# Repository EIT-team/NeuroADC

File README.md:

# NeuroADC
Open Source data acquisition system for biopotential recording and Fast Neural EIT, originally developed by Dr. Enrico Ravagli in 2026.
Contributions are welcome under GPL-3.0 license.

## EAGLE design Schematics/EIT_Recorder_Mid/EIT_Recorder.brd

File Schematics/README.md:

# Schematics
- This subfolder contains design files for the three Printed Circuit Boards which make up the NeuroADC device. Board names are based on their physical location when assembled (top/mid/bottom)
- Boards have been designed using Cad software EAGLE. With EAGLE now being decommissioned in June 2026, board files can be opened and edited in Autodesk Fusion.

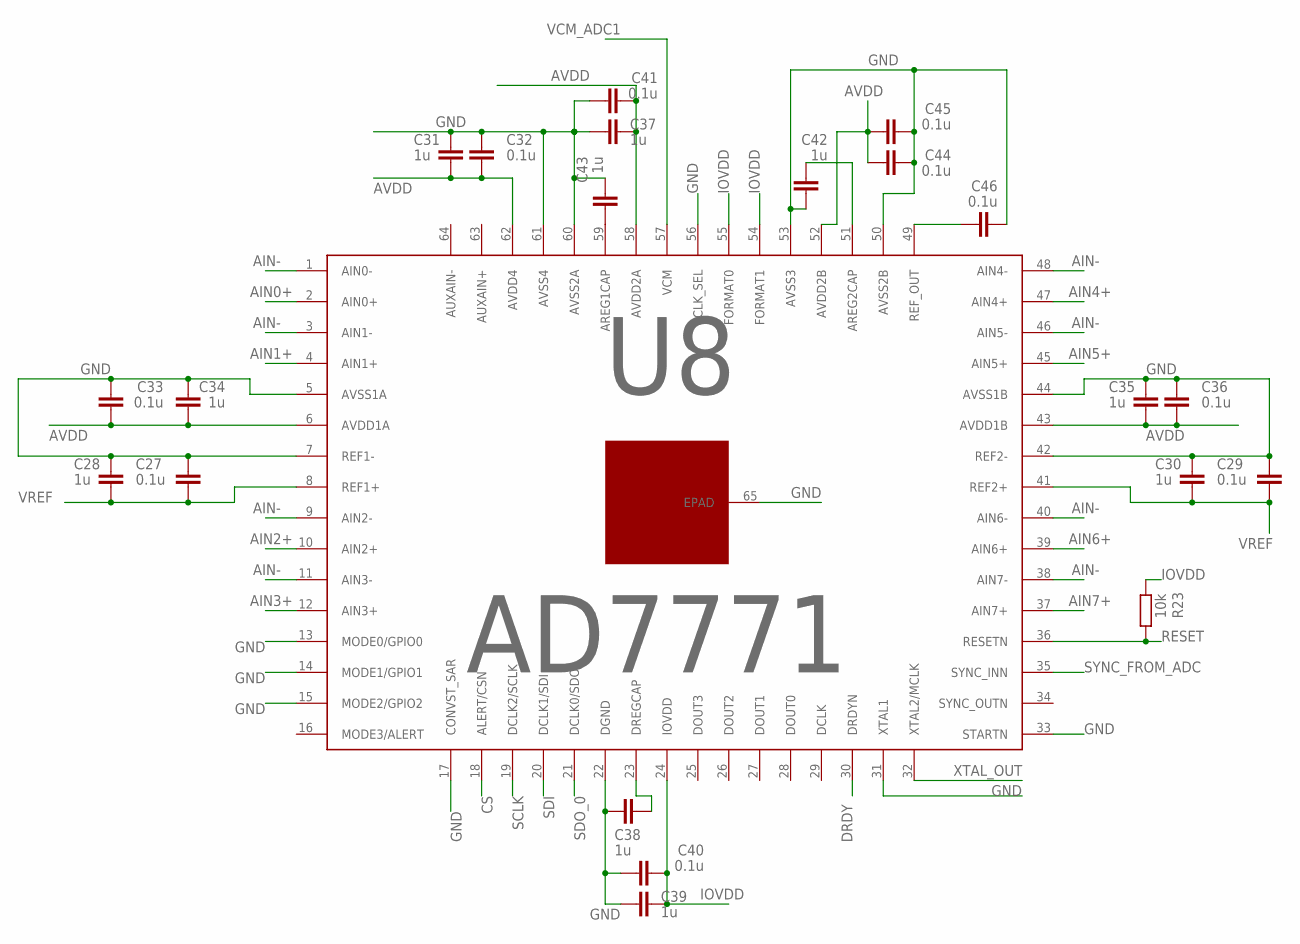
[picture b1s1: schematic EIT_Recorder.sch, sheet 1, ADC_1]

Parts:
C27, C29, C32, C33, C36, C40, C41, C44, C45, C46: 0.1u; C0402
C28, C30, C31, C34, C35, C37, C38, C39, C42, C43: 1u; C0402
R23: 10k; R0603
U8: AD7771; LFCSP64_CUSTOM

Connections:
AIN0+: U8.2 (AIN0+); also elsewhere on the board
AIN1+: U8.4 (AIN1+); also elsewhere on the board
AIN2+: U8.10 (AIN2+); also elsewhere on the board
AIN3+: U8.12 (AIN3+); also elsewhere on the board
AIN4+: U8.47 (AIN4+); also elsewhere on the board
AIN5+: U8.45 (AIN5+); also elsewhere on the board
AIN6+: U8.39 (AIN6+); also elsewhere on the board
AIN7+: U8.37 (AIN7+); also elsewhere on the board
AIN-: U8.1 (AIN0-), U8.3 (AIN1-), U8.9 (AIN2-), U8.11 (AIN3-), U8.38 (AIN7-), U8.40 (AIN6-), U8.46 (AIN5-), U8.48 (AIN4-); also elsewhere on the board
AVDD: C31.1, C32.1, C33.1, C34.1, C35.1, C36.1, C37.1, C41.1, C44.2, C45.2, U8.6 (AVDD1A), U8.43 (AVDD1B), U8.52 (AVDD2B), U8.58 (AVDD2A), U8.62 (AVDD4); also elsewhere on the board
CS: U8.18 (ALERT/CSN); also elsewhere on the board
DRDY: U8.30 (DRDYN); also elsewhere on the board
GND: C27.2, C28.2, C29.2, C30.2, C31.2, C32.2, C33.2, C34.2, C35.2, C36.2, C37.2, C38.1, C39.2, C40.2, C41.2, C42.2, C43.1, C44.1, C45.1, C46.1, U8.5 (AVSS1A), U8.7 (REF1-), U8.13 (MODE0/GPIO0), U8.14 (MODE1/GPIO1), U8.15 (MODE2/GPIO2), U8.17 (CONVST_SAR), U8.22 (DGND), U8.31 (XTAL1), U8.33 (STARTN), U8.42 (REF2-), U8.44 (AVSS1B), U8.50 (AVSS2B), U8.53 (AVSS3), U8.56 (CLK_SEL), U8.60 (AVSS2A), U8.61 (AVSS4), U8.65 (EPAD); also elsewhere on the board
IOVDD: C39.1, C40.1, R23.2, U8.24 (IOVDD), U8.54 (FORMAT1), U8.55 (FORMAT0); also elsewhere on the board
unnamed: C43.2, U8.59 (AREG1CAP)
unnamed: C38.2, U8.23 (DREGCAP)
unnamed: C46.2, U8.49 (REF_OUT)
unnamed: C42.1, U8.51 (AREG2CAP)
RESET: R23.1, U8.36 (RESETN); also elsewhere on the board
SCLK: U8.19 (DCLK2/SCLK); also elsewhere on the board
SDI: U8.20 (DCLK1/SDI); also elsewhere on the board
SDO_0: U8.21 (DCLK0/SDO); also elsewhere on the board
SYNC_FROM_ADC: U8.35 (SYNC_INN); also elsewhere on the board
VCM_ADC1: U8.57 (VCM); also elsewhere on the board
VREF: C27.1, C28.1, C29.1, C30.1, U8.8 (REF1+), U8.41 (REF2+); also elsewhere on the board
XTAL_OUT: U8.32 (XTAL2/MCLK); also elsewhere on the board

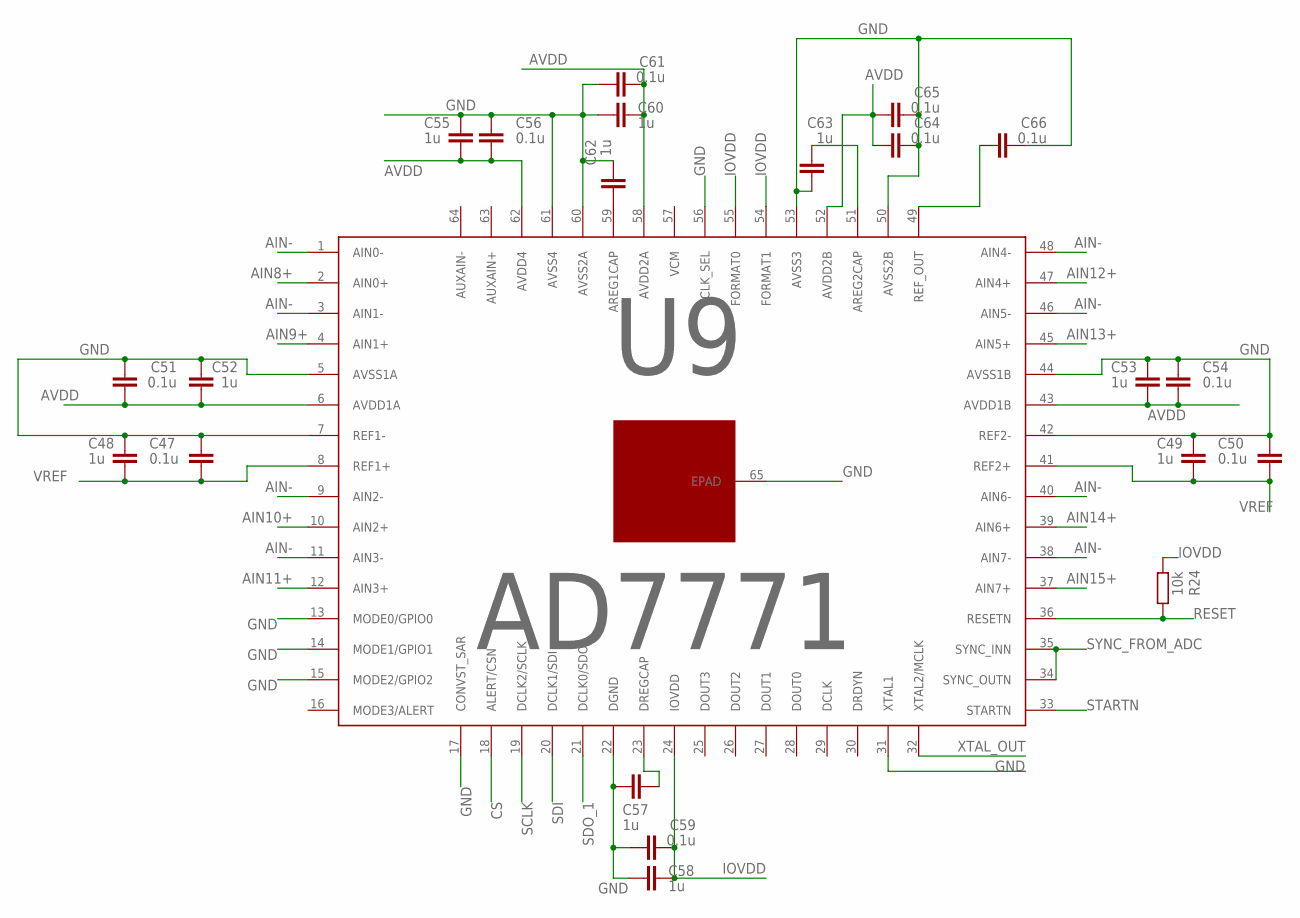
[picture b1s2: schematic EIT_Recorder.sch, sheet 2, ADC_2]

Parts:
C47, C50, C51, C54, C56, C59, C61, C64, C65, C66: 0.1u; C0402
C48, C49, C52, C53, C55, C57, C58, C60, C62, C63: 1u; C0402
R24: 10k; R0603
U9: AD7771; LFCSP64_CUSTOM

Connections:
AIN8+: U9.2 (AIN0+); also elsewhere on the board
AIN9+: U9.4 (AIN1+); also elsewhere on the board
AIN10+: U9.10 (AIN2+); also elsewhere on the board
AIN11+: U9.12 (AIN3+); also elsewhere on the board
AIN12+: U9.47 (AIN4+); also elsewhere on the board
AIN13+: U9.45 (AIN5+); also elsewhere on the board
AIN14+: U9.39 (AIN6+); also elsewhere on the board
AIN15+: U9.37 (AIN7+); also elsewhere on the board
AIN-: U9.1 (AIN0-), U9.3 (AIN1-), U9.9 (AIN2-), U9.11 (AIN3-), U9.38 (AIN7-), U9.40 (AIN6-), U9.46 (AIN5-), U9.48 (AIN4-); also elsewhere on the board
AVDD: C51.1, C52.1, C53.1, C54.1, C55.1, C56.1, C60.1, C61.1, C64.2, C65.2, U9.6 (AVDD1A), U9.43 (AVDD1B), U9.52 (AVDD2B), U9.58 (AVDD2A), U9.62 (AVDD4); also elsewhere on the board
CS: U9.18 (ALERT/CSN); also elsewhere on the board
GND: C47.2, C48.2, C49.2, C50.2, C51.2, C52.2, C53.2, C54.2, C55.2, C56.2, C57.1, C58.2, C59.2, C60.2, C61.2, C62.1, C63.2, C64.1, C65.1, C66.1, U9.5 (AVSS1A), U9.7 (REF1-), U9.13 (MODE0/GPIO0), U9.14 (MODE1/GPIO1), U9.15 (MODE2/GPIO2), U9.17 (CONVST_SAR), U9.22 (DGND), U9.31 (XTAL1), U9.42 (REF2-), U9.44 (AVSS1B), U9.50 (AVSS2B), U9.53 (AVSS3), U9.56 (CLK_SEL), U9.60 (AVSS2A), U9.61 (AVSS4), U9.65 (EPAD); also elsewhere on the board
IOVDD: C58.1, C59.1, R24.2, U9.24 (IOVDD), U9.54 (FORMAT1), U9.55 (FORMAT0); also elsewhere on the board
unnamed: C57.2, U9.23 (DREGCAP)
unnamed: C62.2, U9.59 (AREG1CAP)
unnamed: C63.1, U9.51 (AREG2CAP)
unnamed: C66.2, U9.49 (REF_OUT)
RESET: R24.1, U9.36 (RESETN); also elsewhere on the board
SCLK: U9.19 (DCLK2/SCLK); also elsewhere on the board
SDI: U9.20 (DCLK1/SDI); also elsewhere on the board
SDO_1: U9.21 (DCLK0/SDO); also elsewhere on the board
STARTN: U9.33 (STARTN); also elsewhere on the board
SYNC_FROM_ADC: U9.34 (SYNC_OUTN), U9.35 (SYNC_INN); also elsewhere on the board
VREF: C47.1, C48.1, C49.1, C50.1, U9.8 (REF1+), U9.41 (REF2+); also elsewhere on the board
XTAL_OUT: U9.32 (XTAL2/MCLK); also elsewhere on the board

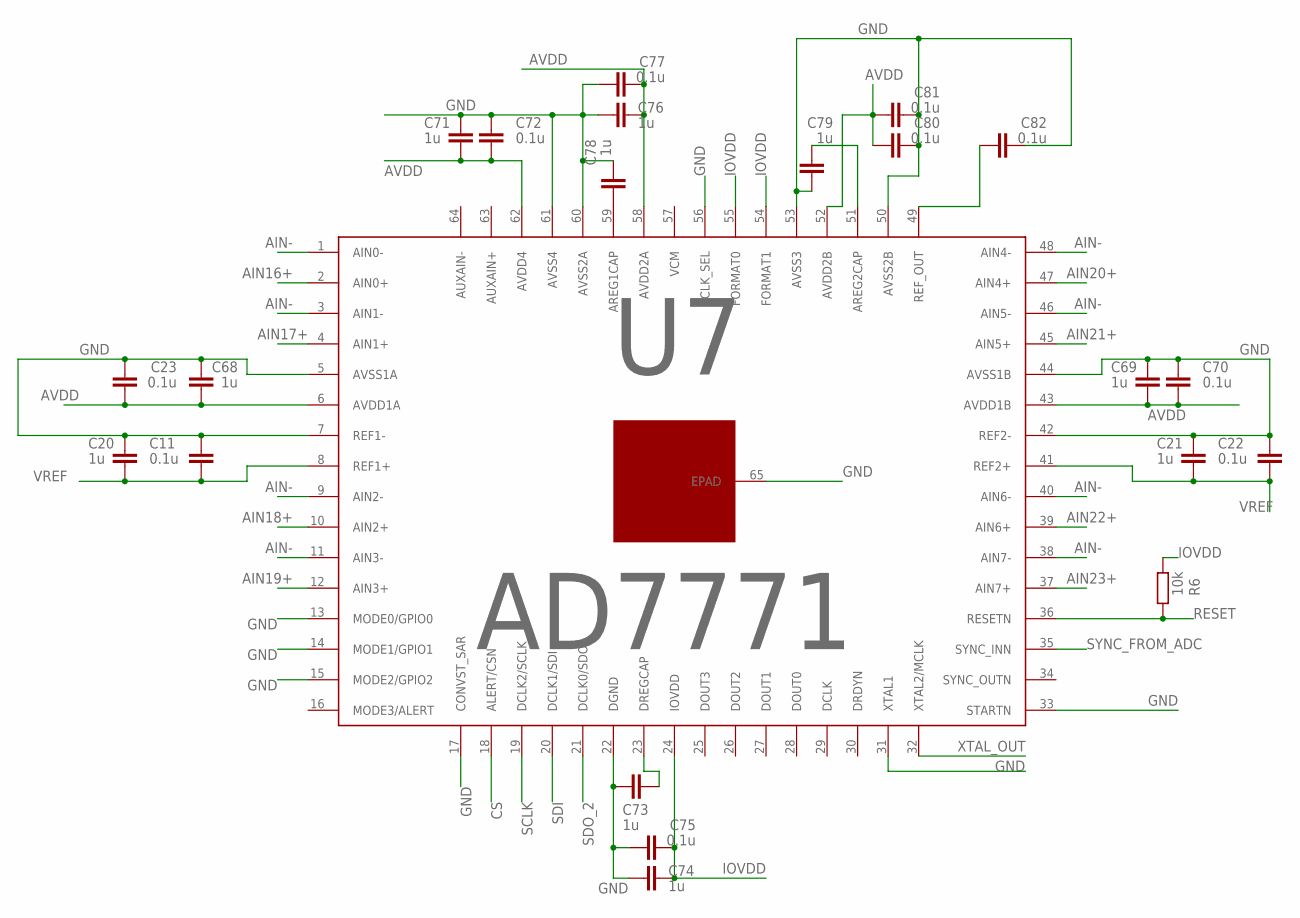
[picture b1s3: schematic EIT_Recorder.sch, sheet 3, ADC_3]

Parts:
C11, C22, C23, C70, C72, C75, C77, C80, C81, C82: 0.1u; C0402
C20, C21, C68, C69, C71, C73, C74, C76, C78, C79: 1u; C0402
R6: 10k; R0603
U7: AD7771; LFCSP64_CUSTOM

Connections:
AIN16+: U7.2 (AIN0+); also elsewhere on the board
AIN17+: U7.4 (AIN1+); also elsewhere on the board
AIN18+: U7.10 (AIN2+); also elsewhere on the board
AIN19+: U7.12 (AIN3+); also elsewhere on the board
AIN20+: U7.47 (AIN4+); also elsewhere on the board
AIN21+: U7.45 (AIN5+); also elsewhere on the board
AIN22+: U7.39 (AIN6+); also elsewhere on the board
AIN23+: U7.37 (AIN7+); also elsewhere on the board
AIN-: U7.1 (AIN0-), U7.3 (AIN1-), U7.9 (AIN2-), U7.11 (AIN3-), U7.38 (AIN7-), U7.40 (AIN6-), U7.46 (AIN5-), U7.48 (AIN4-); also elsewhere on the board
AVDD: C23.1, C68.1, C69.1, C70.1, C71.1, C72.1, C76.1, C77.1, C80.2, C81.2, U7.6 (AVDD1A), U7.43 (AVDD1B), U7.52 (AVDD2B), U7.58 (AVDD2A), U7.62 (AVDD4); also elsewhere on the board
CS: U7.18 (ALERT/CSN); also elsewhere on the board
GND: C11.2, C20.2, C21.2, C22.2, C23.2, C68.2, C69.2, C70.2, C71.2, C72.2, C73.1, C74.2, C75.2, C76.2, C77.2, C78.1, C79.2, C80.1, C81.1, C82.1, U7.5 (AVSS1A), U7.7 (REF1-), U7.13 (MODE0/GPIO0), U7.14 (MODE1/GPIO1), U7.15 (MODE2/GPIO2), U7.17 (CONVST_SAR), U7.22 (DGND), U7.31 (XTAL1), U7.33 (STARTN), U7.42 (REF2-), U7.44 (AVSS1B), U7.50 (AVSS2B), U7.53 (AVSS3), U7.56 (CLK_SEL), U7.60 (AVSS2A), U7.61 (AVSS4), U7.65 (EPAD); also elsewhere on the board
IOVDD: C74.1, C75.1, R6.2, U7.24 (IOVDD), U7.54 (FORMAT1), U7.55 (FORMAT0); also elsewhere on the board
unnamed: C73.2, U7.23 (DREGCAP)
unnamed: C78.2, U7.59 (AREG1CAP)
unnamed: C79.1, U7.51 (AREG2CAP)
unnamed: C82.2, U7.49 (REF_OUT)
RESET: R6.1, U7.36 (RESETN); also elsewhere on the board
SCLK: U7.19 (DCLK2/SCLK); also elsewhere on the board
SDI: U7.20 (DCLK1/SDI); also elsewhere on the board
SDO_2: U7.21 (DCLK0/SDO); also elsewhere on the board
SYNC_FROM_ADC: U7.35 (SYNC_INN); also elsewhere on the board
VREF: C11.1, C20.1, C21.1, C22.1, U7.8 (REF1+), U7.41 (REF2+); also elsewhere on the board
XTAL_OUT: U7.32 (XTAL2/MCLK); also elsewhere on the board

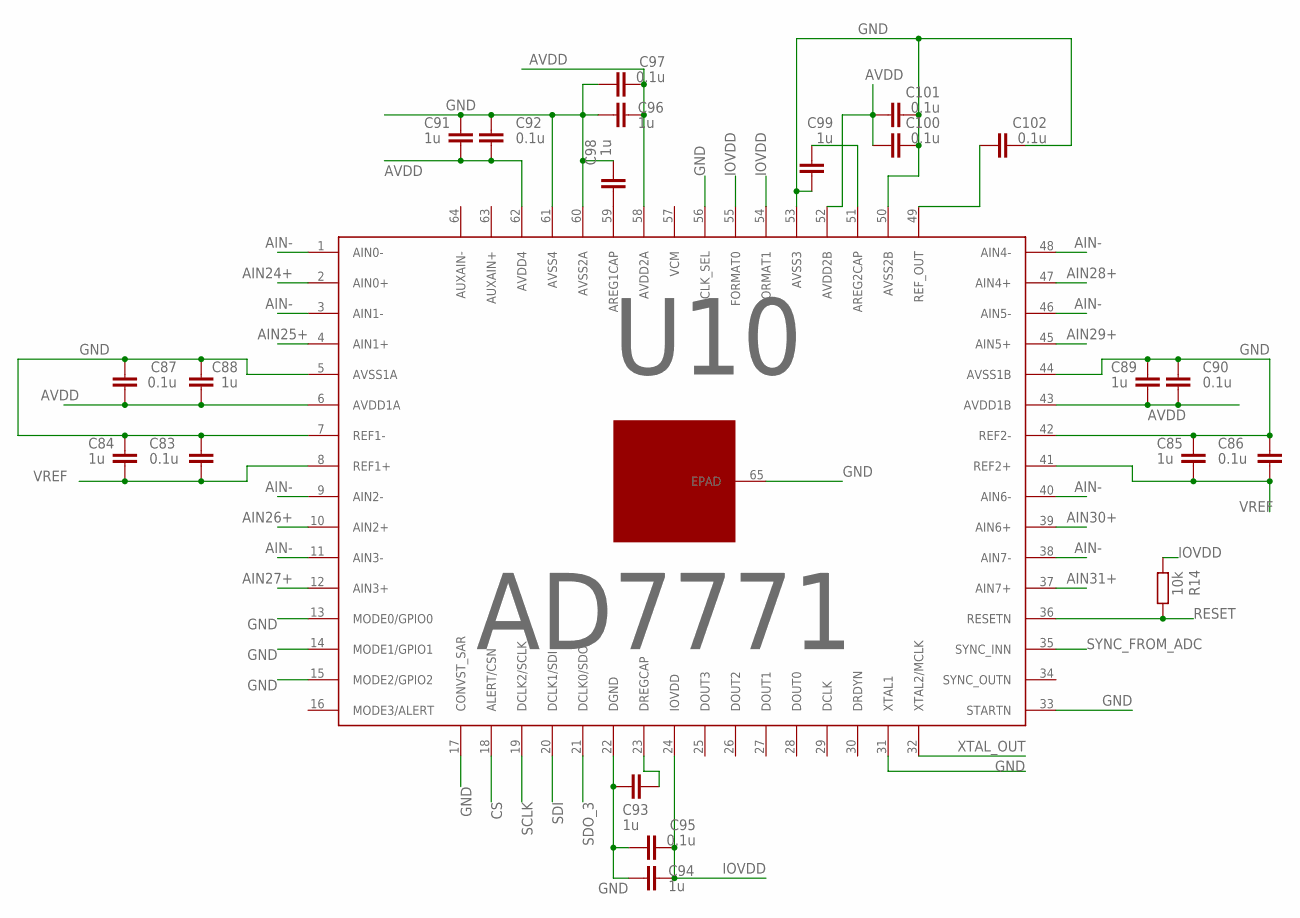
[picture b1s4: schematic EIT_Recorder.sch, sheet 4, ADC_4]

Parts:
C83, C86, C87, C90, C92, C95, C97, C100, C101, C102: 0.1u; C0402
C84, C85, C88, C89, C91, C93, C94, C96, C98, C99: 1u; C0402
R14: 10k; R0603
U10: AD7771; LFCSP64_CUSTOM

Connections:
AIN24+: U10.2 (AIN0+); also elsewhere on the board
AIN25+: U10.4 (AIN1+); also elsewhere on the board
AIN26+: U10.10 (AIN2+); also elsewhere on the board
AIN27+: U10.12 (AIN3+); also elsewhere on the board
AIN28+: U10.47 (AIN4+); also elsewhere on the board
AIN29+: U10.45 (AIN5+); also elsewhere on the board
AIN30+: U10.39 (AIN6+); also elsewhere on the board
AIN31+: U10.37 (AIN7+); also elsewhere on the board
AIN-: U10.1 (AIN0-), U10.3 (AIN1-), U10.9 (AIN2-), U10.11 (AIN3-), U10.38 (AIN7-), U10.40 (AIN6-), U10.46 (AIN5-), U10.48 (AIN4-); also elsewhere on the board
AVDD: C87.1, C88.1, C89.1, C90.1, C91.1, C92.1, C96.1, C97.1, C100.2, C101.2, U10.6 (AVDD1A), U10.43 (AVDD1B), U10.52 (AVDD2B), U10.58 (AVDD2A), U10.62 (AVDD4); also elsewhere on the board
CS: U10.18 (ALERT/CSN); also elsewhere on the board
GND: C83.2, C84.2, C85.2, C86.2, C87.2, C88.2, C89.2, C90.2, C91.2, C92.2, C93.1, C94.2, C95.2, C96.2, C97.2, C98.1, C99.2, C100.1, C101.1, C102.1, U10.5 (AVSS1A), U10.7 (REF1-), U10.13 (MODE0/GPIO0), U10.14 (MODE1/GPIO1), U10.15 (MODE2/GPIO2), U10.17 (CONVST_SAR), U10.22 (DGND), U10.31 (XTAL1), U10.33 (STARTN), U10.42 (REF2-), U10.44 (AVSS1B), U10.50 (AVSS2B), U10.53 (AVSS3), U10.56 (CLK_SEL), U10.60 (AVSS2A), U10.61 (AVSS4), U10.65 (EPAD); also elsewhere on the board
IOVDD: C94.1, C95.1, R14.2, U10.24 (IOVDD), U10.54 (FORMAT1), U10.55 (FORMAT0); also elsewhere on the board
unnamed: C93.2, U10.23 (DREGCAP)
unnamed: C98.2, U10.59 (AREG1CAP)
unnamed: C99.1, U10.51 (AREG2CAP)
unnamed: C102.2, U10.49 (REF_OUT)
RESET: R14.1, U10.36 (RESETN); also elsewhere on the board
SCLK: U10.19 (DCLK2/SCLK); also elsewhere on the board
SDI: U10.20 (DCLK1/SDI); also elsewhere on the board
SDO_3: U10.21 (DCLK0/SDO); also elsewhere on the board
SYNC_FROM_ADC: U10.35 (SYNC_INN); also elsewhere on the board
VREF: C83.1, C84.1, C85.1, C86.1, U10.8 (REF1+), U10.41 (REF2+); also elsewhere on the board
XTAL_OUT: U10.32 (XTAL2/MCLK); also elsewhere on the board

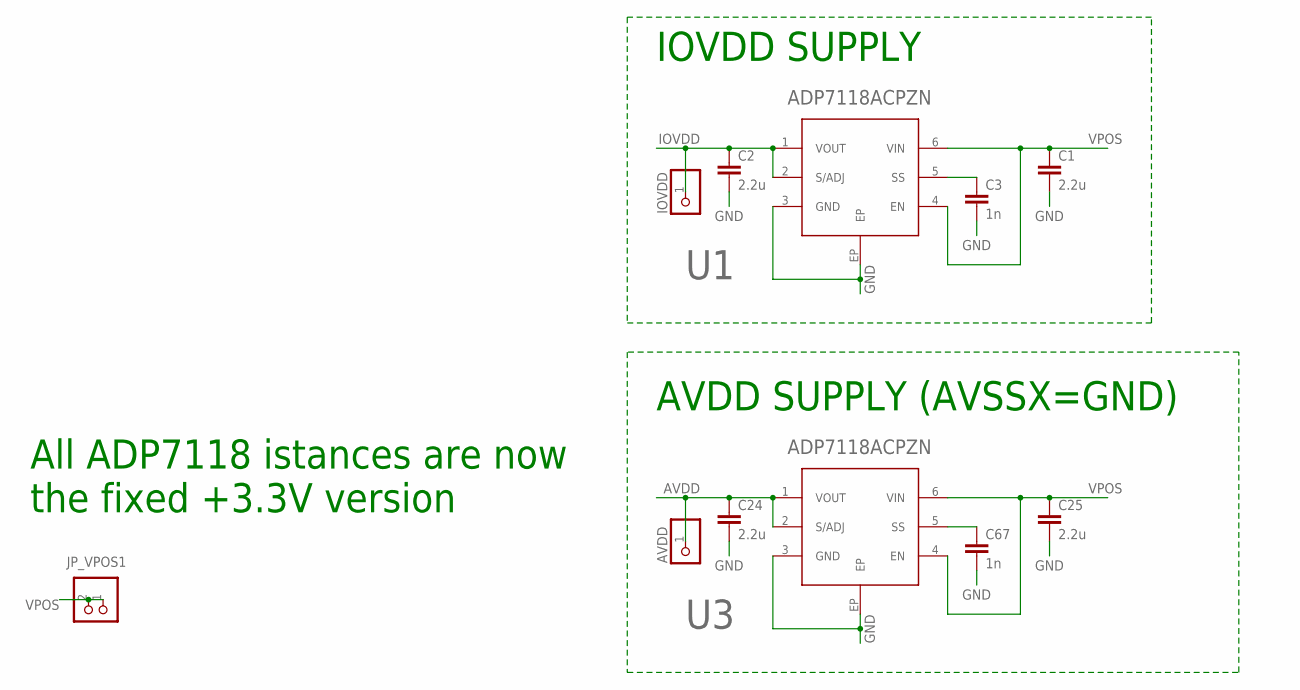
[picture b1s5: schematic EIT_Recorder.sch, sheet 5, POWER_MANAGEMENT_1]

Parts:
AVDD: PINHD-1X1; 1X01
C1, C2, C24, C25: 2.2u; C0603
C3, C67: 1n; C0402
IOVDD: PINHD-1X1; 1X01
JP_VPOS1: PINHD-1X2; 1X02
U1, U3: ADP7118ACPZN; LFCSP6_CUSTOM

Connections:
AVDD: AVDD.1, C24.1, U3.1 (VOUT), U3.2 (S/ADJ); also elsewhere on the board
GND: C1.2, C2.2, C3.2, C24.2, C25.2, C67.2, U1.3 (GND), U1.EP, U3.3 (GND), U3.EP; also elsewhere on the board
IOVDD: C2.1, IOVDD.1, U1.1 (VOUT), U1.2 (S/ADJ); also elsewhere on the board
unnamed: C3.1, U1.5 (SS)
unnamed: C67.1, U3.5 (SS)
VPOS: C1.1, C25.1, JP_VPOS1.1, JP_VPOS1.2, U1.4 (EN), U1.6 (VIN), U3.4 (EN), U3.6 (VIN); also elsewhere on the board

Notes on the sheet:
IOVDD SUPPLY
AVDD SUPPLY (AVSSX=GND)
All ADP7118 istances are now the fixed +3.3V version

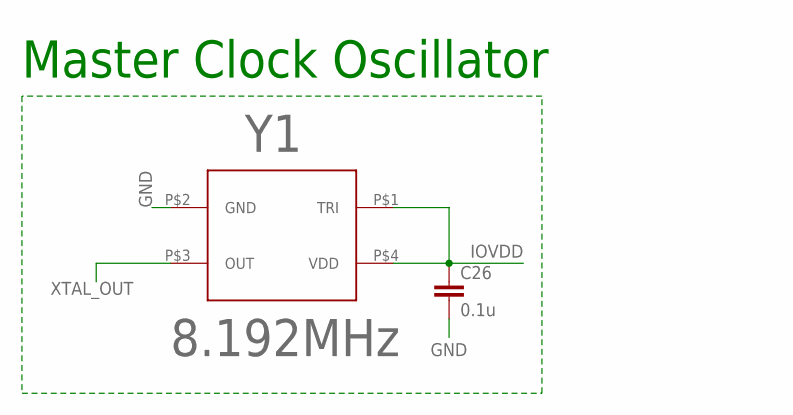
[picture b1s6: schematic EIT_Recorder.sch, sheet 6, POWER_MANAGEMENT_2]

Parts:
C26: 0.1u; C0402
Y1: 8.192MHz; ECS-2520MVLC

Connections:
GND: C26.2, Y1.P$2 (GND); also elsewhere on the board
IOVDD: C26.1, Y1.P$1 (TRI), Y1.P$4 (VDD); also elsewhere on the board
XTAL_OUT: Y1.P$3 (OUT); also elsewhere on the board

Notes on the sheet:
Master Clock Oscillator

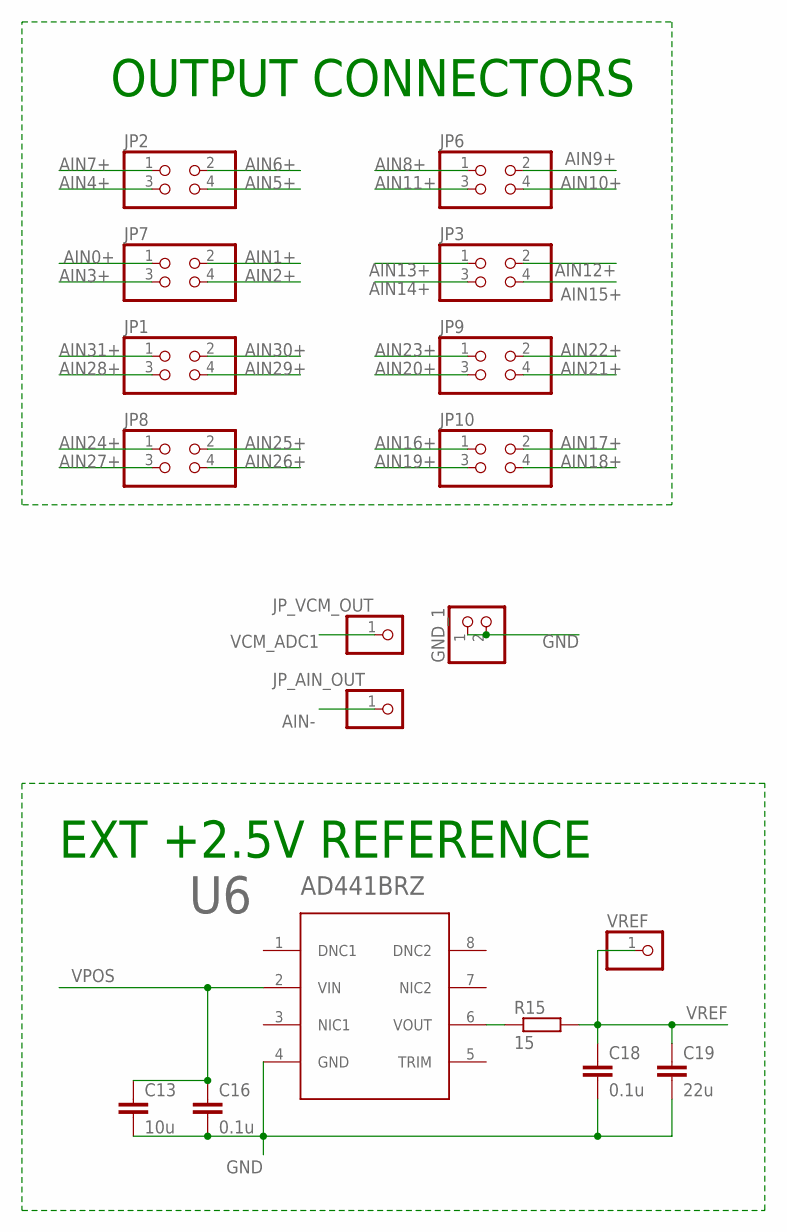
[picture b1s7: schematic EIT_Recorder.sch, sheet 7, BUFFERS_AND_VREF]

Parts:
C13: 10u; C0805
C16, C18: 0.1u; C0402
C19: 22u; C0805
GND_1: PINHD-1X2; 1X02
JP1, JP2, JP3, JP6, JP7, JP8, JP9, JP10: PINHD-2X2; 2X02
JP_AIN_OUT: PINHD-1X1; 1X01
JP_VCM_OUT: PINHD-1X1; 1X01
R15: 15; R0603
U6: AD441BRZ; SOIC8N_CUSTOM
VREF: PINHD-1X1; 1X01

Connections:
AIN0+: JP7.1; also elsewhere on the board
AIN1+: JP7.2; also elsewhere on the board
AIN2+: JP7.4; also elsewhere on the board
AIN3+: JP7.3; also elsewhere on the board
AIN4+: JP2.3; also elsewhere on the board
AIN5+: JP2.4; also elsewhere on the board
AIN6+: JP2.2; also elsewhere on the board
AIN7+: JP2.1; also elsewhere on the board
AIN8+: JP6.1; also elsewhere on the board
AIN9+: JP6.2; also elsewhere on the board
AIN10+: JP6.4; also elsewhere on the board
AIN11+: JP6.3; also elsewhere on the board
AIN12+: JP3.2; also elsewhere on the board
AIN13+: JP3.1; also elsewhere on the board
AIN14+: JP3.3; also elsewhere on the board
AIN15+: JP3.4; also elsewhere on the board
AIN16+: JP10.1; also elsewhere on the board
AIN17+: JP10.2; also elsewhere on the board
AIN18+: JP10.4; also elsewhere on the board
AIN19+: JP10.3; also elsewhere on the board
AIN20+: JP9.3; also elsewhere on the board
AIN21+: JP9.4; also elsewhere on the board
AIN22+: JP9.2; also elsewhere on the board
AIN23+: JP9.1; also elsewhere on the board
AIN24+: JP8.1; also elsewhere on the board
AIN25+: JP8.2; also elsewhere on the board
AIN26+: JP8.4; also elsewhere on the board
AIN27+: JP8.3; also elsewhere on the board
AIN28+: JP1.3; also elsewhere on the board
AIN29+: JP1.4; also elsewhere on the board
AIN30+: JP1.2; also elsewhere on the board
AIN31+: JP1.1; also elsewhere on the board
AIN-: JP_AIN_OUT.1; also elsewhere on the board
GND: C13.2, C16.2, C18.2, C19.2, GND_1.1, GND_1.2, U6.4 (GND); also elsewhere on the board
unnamed: R15.1, U6.6 (VOUT)
VCM_ADC1: JP_VCM_OUT.1; also elsewhere on the board
VPOS: C13.1, C16.1, U6.2 (VIN); also elsewhere on the board
VREF: C18.1, C19.1, R15.2, VREF.1; also elsewhere on the board

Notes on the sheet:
EXT +2.5V REFERENCE
OUTPUT CONNECTORS

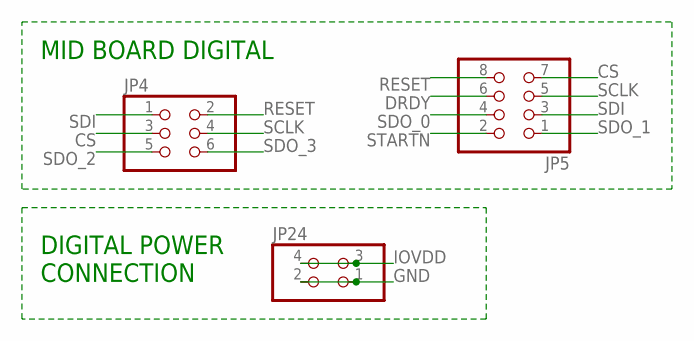
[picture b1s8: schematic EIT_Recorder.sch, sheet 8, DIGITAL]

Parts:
JP4: PINHD-2X3; 2X03
JP5: PINHD-2X4; 2X04
JP24: PINHD-2X2; 2X02

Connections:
CS: JP4.3, JP5.7; also elsewhere on the board
DRDY: JP5.6; also elsewhere on the board
GND: JP24.1, JP24.2; also elsewhere on the board
IOVDD: JP24.3, JP24.4; also elsewhere on the board
RESET: JP4.2, JP5.8; also elsewhere on the board
SCLK: JP4.4, JP5.5; also elsewhere on the board
SDI: JP4.1, JP5.3; also elsewhere on the board
SDO_0: JP5.4; also elsewhere on the board
SDO_1: JP5.1; also elsewhere on the board
SDO_2: JP4.5; also elsewhere on the board
SDO_3: JP4.6; also elsewhere on the board
STARTN: JP5.2; also elsewhere on the board

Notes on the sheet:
MID BOARD DIGITAL
DIGITAL POWER CONNECTION

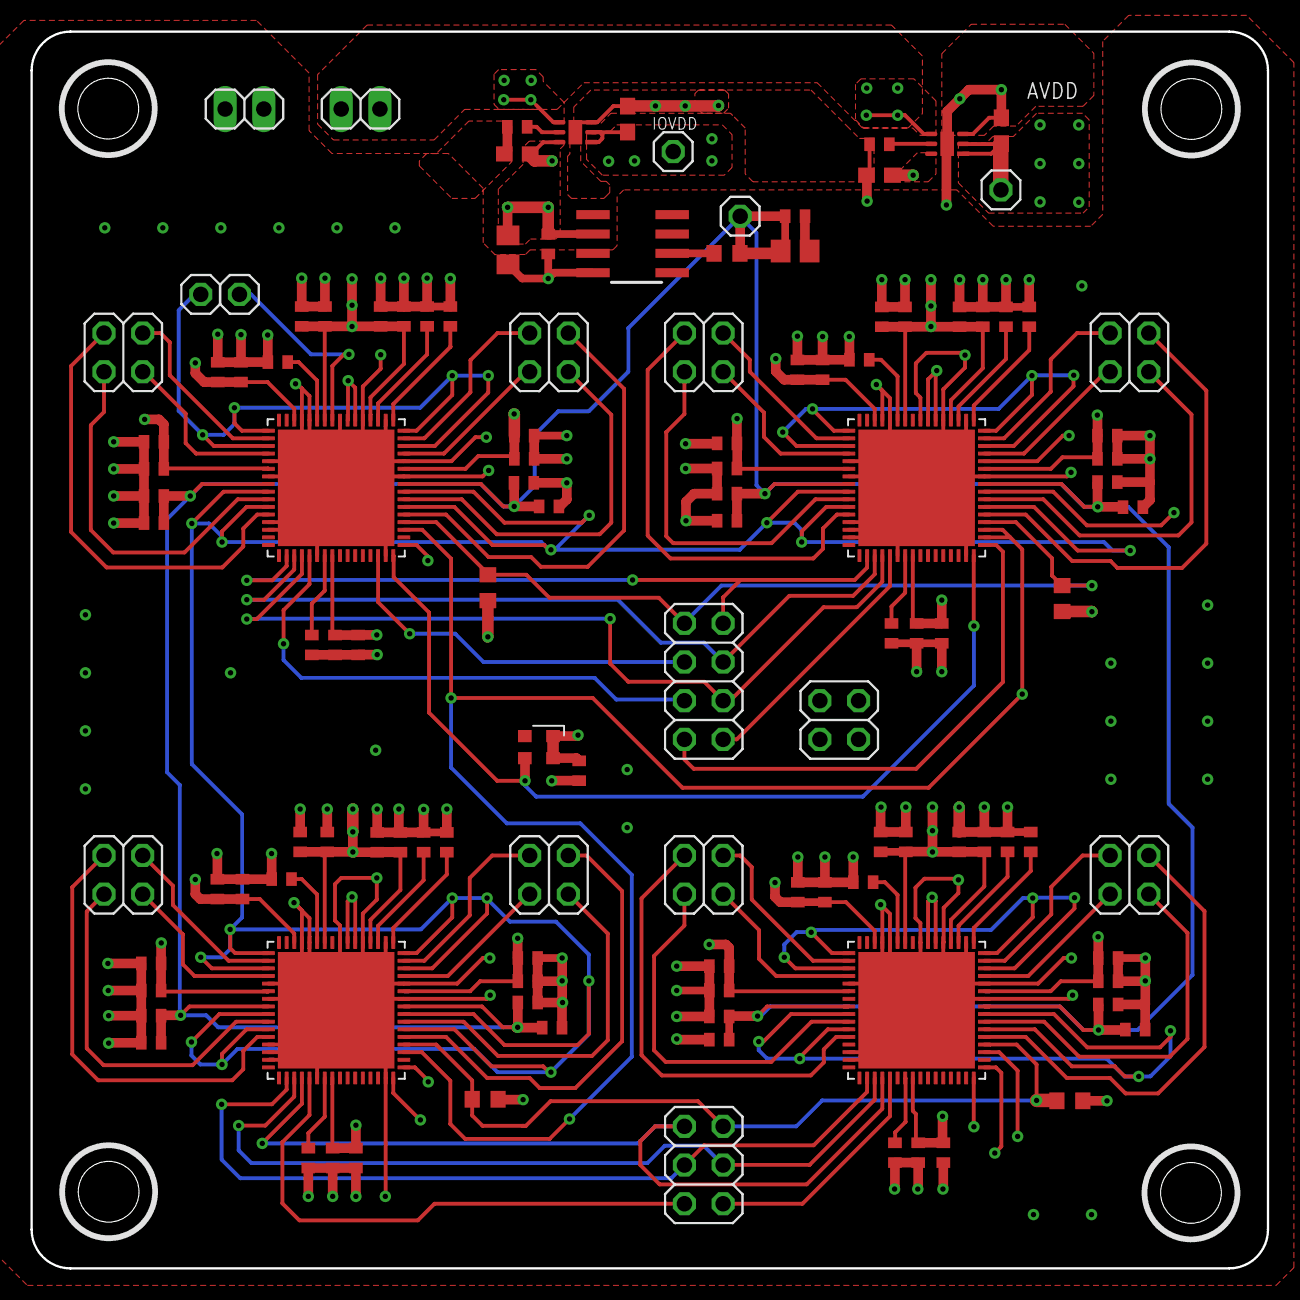
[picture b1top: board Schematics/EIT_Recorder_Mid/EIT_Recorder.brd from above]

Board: 6 copper layers, 81.2 x 81.2 mm, 122 parts (0 on the bottom side), 70 nets.

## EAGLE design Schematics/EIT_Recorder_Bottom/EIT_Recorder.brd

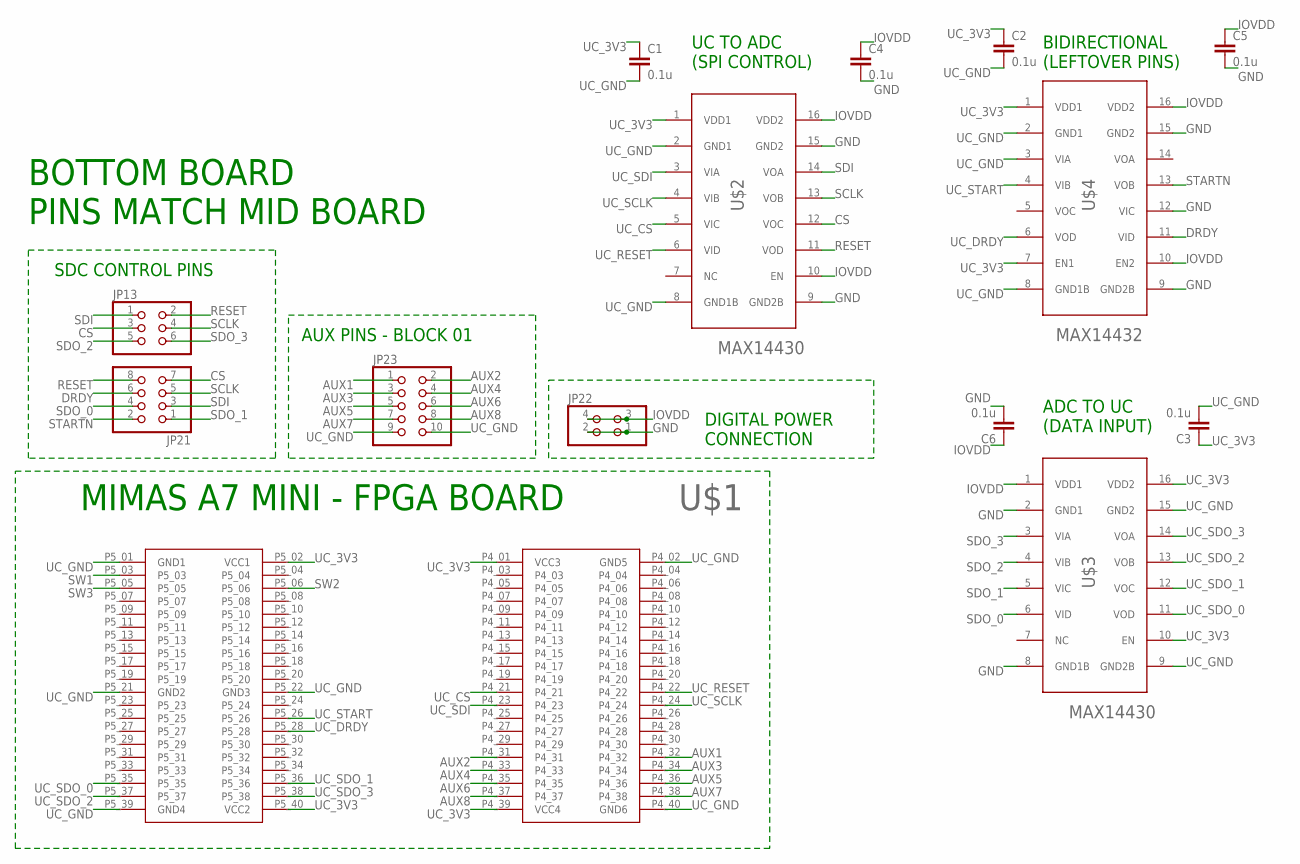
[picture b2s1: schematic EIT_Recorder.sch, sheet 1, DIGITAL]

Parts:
C1, C2, C3, C4, C5, C6: 0.1u; C0805
JP13: PINHD-2X3; 2X03
JP21: PINHD-2X4; 2X04
JP22: PINHD-2X2; 2X02
JP23: PINHD-2X5/90; 2X05/90
U$1: MIMAS_A7_MINI
U$2, U$3: MAX14430; SOIC16_CUSTOM
U$4: MAX14432; SOIC16_CUSTOM

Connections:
AUX1: JP23.1, U$1.P4_32
AUX2: JP23.2, U$1.P4_31
AUX3: JP23.3, U$1.P4_34
AUX4: JP23.4, U$1.P4_33
AUX5: JP23.5, U$1.P4_36
AUX6: JP23.6, U$1.P4_35
AUX7: JP23.7, U$1.P4_38
AUX8: JP23.8, U$1.P4_37
CS: JP13.3, JP21.7, U$2.12 (VOC)
DRDY: JP21.6, U$4.11 (VID)
GND: C4.2, C5.2, C6.2, JP22.1, JP22.2, U$2.9 (GND2B), U$2.15 (GND2), U$3.2 (GND1), U$3.8 (GND1B), U$4.9 (GND2B), U$4.12 (VIC), U$4.15 (GND2)
IOVDD: C4.1, C5.1, C6.1, JP22.3, JP22.4, U$2.10 (EN), U$2.16 (VDD2), U$3.1 (VDD1), U$4.10 (EN2), U$4.16 (VDD2)
RESET: JP13.2, JP21.8, U$2.11 (VOD)
SCLK: JP13.4, JP21.5, U$2.13 (VOB)
SDI: JP13.1, JP21.3, U$2.14 (VOA)
SDO_0: JP21.4, U$3.6 (VID)
SDO_1: JP21.1, U$3.5 (VIC)
SDO_2: JP13.5, U$3.4 (VIB)
SDO_3: JP13.6, U$3.3 (VIA)
STARTN: JP21.2, U$4.13 (VOB)
SW1: U$1.P5_03; also elsewhere on the board
SW2: U$1.P5_06; also elsewhere on the board
SW3: U$1.P5_05; also elsewhere on the board
UC_3V3: C1.1, C2.1, C3.1, U$1.P4_01 (VCC3), U$1.P4_39 (VCC4), U$1.P5_02 (VCC1), U$1.P5_40 (VCC2), U$2.1 (VDD1), U$3.10 (EN), U$3.16 (VDD2), U$4.1 (VDD1), U$4.7 (EN1); also elsewhere on the board
UC_CS: U$1.P4_21, U$2.5 (VIC)
UC_DRDY: U$1.P5_28, U$4.6 (VOD)
UC_GND: C1.2, C2.2, C3.2, JP23.9, JP23.10, U$1.P4_02 (GND5), U$1.P4_40 (GND6), U$1.P5_01 (GND1), U$1.P5_21 (GND2), U$1.P5_22 (GND3), U$1.P5_39 (GND4), U$2.2 (GND1), U$2.8 (GND1B), U$3.9 (GND2B), U$3.15 (GND2), U$4.2 (GND1), U$4.3 (VIA), U$4.8 (GND1B); also elsewhere on the board
UC_RESET: U$1.P4_22, U$2.6 (VID)
UC_SCLK: U$1.P4_24, U$2.4 (VIB)
UC_SDI: U$1.P4_23, U$2.3 (VIA)
UC_SDO_0: U$1.P5_35, U$3.11 (VOD)
UC_SDO_1: U$1.P5_36, U$3.12 (VOC)
UC_SDO_2: U$1.P5_37, U$3.13 (VOB)
UC_SDO_3: U$1.P5_38, U$3.14 (VOA)
UC_START: U$1.P5_26, U$4.4 (VIB)

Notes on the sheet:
UC TO ADC (SPI CONTROL)
ADC TO UC (DATA INPUT)
BIDIRECTIONAL (LEFTOVER PINS)
MIMAS A7 MINI - FPGA BOARD
BOTTOM BOARD PINS MATCH MID BOARD
SDC CONTROL PINS
AUX PINS - BLOCK 01
DIGITAL POWER CONNECTION

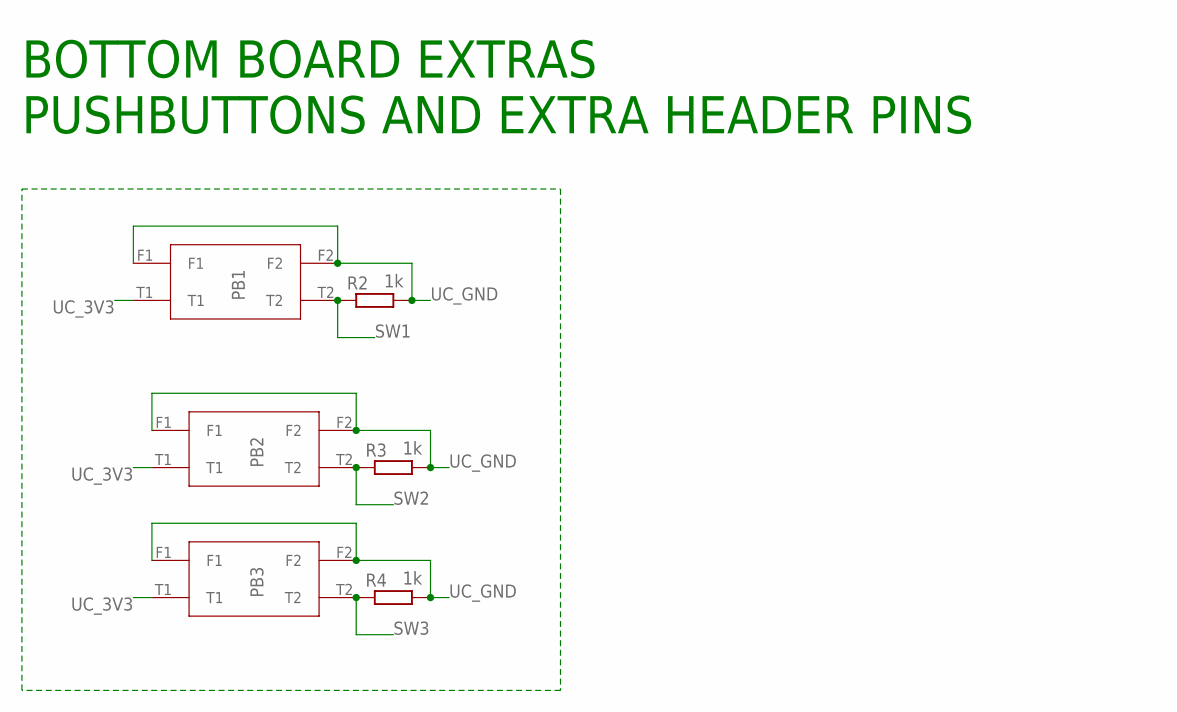
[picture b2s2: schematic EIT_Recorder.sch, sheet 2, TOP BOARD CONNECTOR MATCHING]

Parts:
PB1, PB2, PB3: PUSHBUTTON_95C06B2RAT
R2, R3, R4: 1k; R0805

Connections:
SW1: PB1.T2, R2.1; also elsewhere on the board
SW2: PB2.T2, R3.1; also elsewhere on the board
SW3: PB3.T2, R4.1; also elsewhere on the board
UC_3V3: PB1.T1, PB2.T1, PB3.T1; also elsewhere on the board
UC_GND: PB1.F1, PB1.F2, PB2.F1, PB2.F2, PB3.F1, PB3.F2, R2.2, R3.2, R4.2; also elsewhere on the board

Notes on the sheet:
BOTTOM BOARD EXTRAS PUSHBUTTONS AND EXTRA HEADER PINS

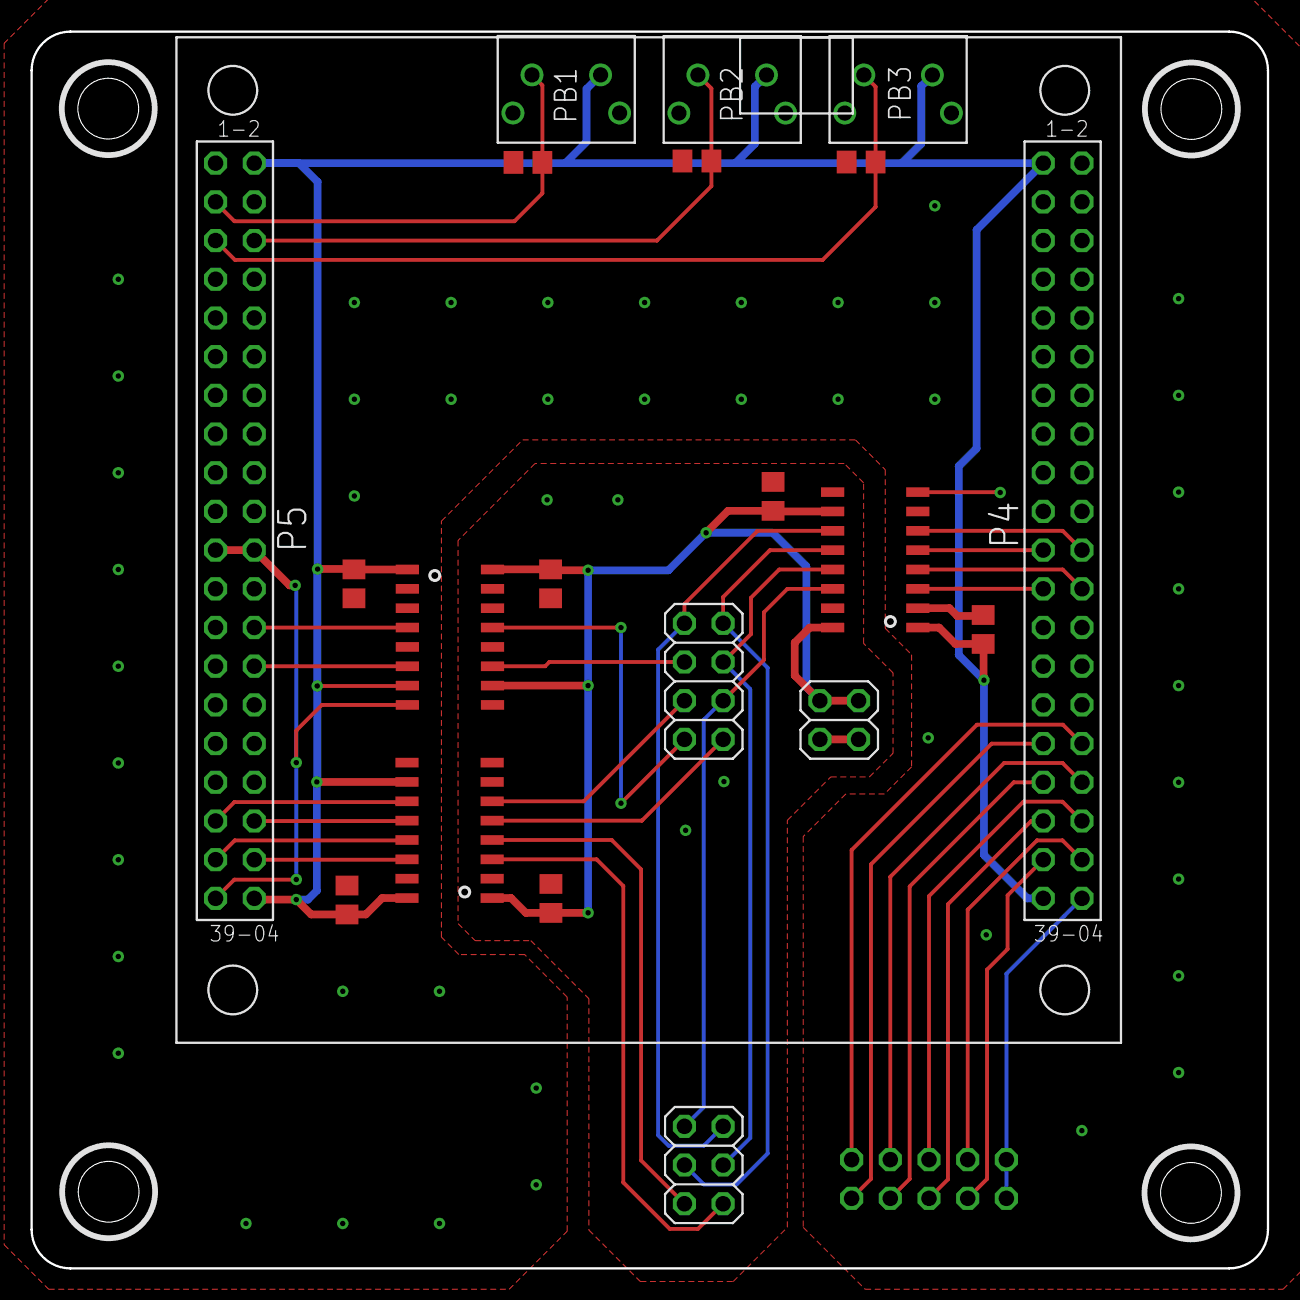
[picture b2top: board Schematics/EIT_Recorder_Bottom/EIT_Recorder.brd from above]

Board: 2 copper layers, 81.2 x 81.2 mm, 20 parts (1 on the bottom side), 35 nets.
